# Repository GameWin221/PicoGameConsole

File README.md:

# Shamino Console
My own game console powered by Raspberry Pi Pico and ST7735 LCD display.

### Software Design
The console framework is made to be **elegant**, **readable** and as **performant** as possible. It is written in C++ only for some convenience features and most of it is almost pure embedded-style C. Thanks to the functional and modular code structure it is easy to port it for other platforms.

You can make your own game just by declaring a new `GameInfo` inside `games_list.hpp` file and defining its functions inside other `.cpp` file. (Look at other example games provided in the repository)

### Hardware Design
The new improved version of the "Shamino Console" now features a custom PCB. This greatly improves the general quality of the console. It just looks and feels better now :)

There will be a 3D printed casing for it soon.

To see the old version, look inside the `/old_design` directory.

### Required componnts:
- [Raspberry Pi Pico (W)](https://www.raspberrypi.com/products/raspberry-pi-pico/)

- [Waveshare ST7735 1.8" LCD](https://www.waveshare.com/wiki/1.8inch_LCD_Module)

- [Generic Thumb Joystick](https://botland.store/joystick/1942-thumb-joystick-5904422356231.html)

- 2x [12mm x 12mm Tact Switches](https://botland.store/tact-switch/3663-tact-switch-12x12mm-with-cap-red-mushroom-5pcs-5904422307486.html)

- [Female Connectors for Raspberry Pi Pico](https://botland.store/raspberry-pi-pico-accessories/18863-set-of-female-connectors-for-raspberry-pi-pico-5904422328528.html)

- [5V 12mm Passive Buzzer](https://botland.store/buzzers-sound-generators/18290-buzzer-without-generator-5v-1mm-tht-5904422366025.html)

- ~47Ω Resistor

- ~4,7kΩ Resistor

- [1x8 Goldpin connector](https://botland.store/connectors-goldpin/20031-straight-goldpin-1x40-connector-with-254mm-pitch-black-10pcs-justpi-5904422329198.html)

- (Optional) 2x 5mm M3 Screw to mount the LCD

- 4x 10mm M3 Screws to mount the PCB to the 3D printed casing.

- [Battery Holder for 2x AA batteries **with a power switch** (3x AA batteries will work fine too)](https://botland.store/battery-holders/738-battery-holder-for-2-aa-r6-batteries-with-cover-and-switch-5904422329617.html)

# How to compile? 
### Prerequisites
- [Pico SDK](https://github.com/raspberrypi/pico-sdk) (St the `PICO_SDK_PATH` enviromental variable)
- [ARM Toolchain](https://developer.arm.com/downloads/-/arm-gnu-toolchain-downloads) (Set the `PICO_TOOLCHAIN_PATH` enviromental variable)
- [CMake](https://cmake.org/) (Add to path)
- [MinGW](https://winlibs.com/) or other C++ compiler (Add to path)

### Commands (Using MinGW):
1. `mkdir build && cd build`
2. `cmake -G "MinGW Makefiles" ..`
3. `make` or `mingw32-make`
4. If everything compiled successfully - copy the `GameOnConsole.uf2` file to your Pico

On Windows you can use the `run.bat` script (You will most likely need to specify the target drive which is your Pico)

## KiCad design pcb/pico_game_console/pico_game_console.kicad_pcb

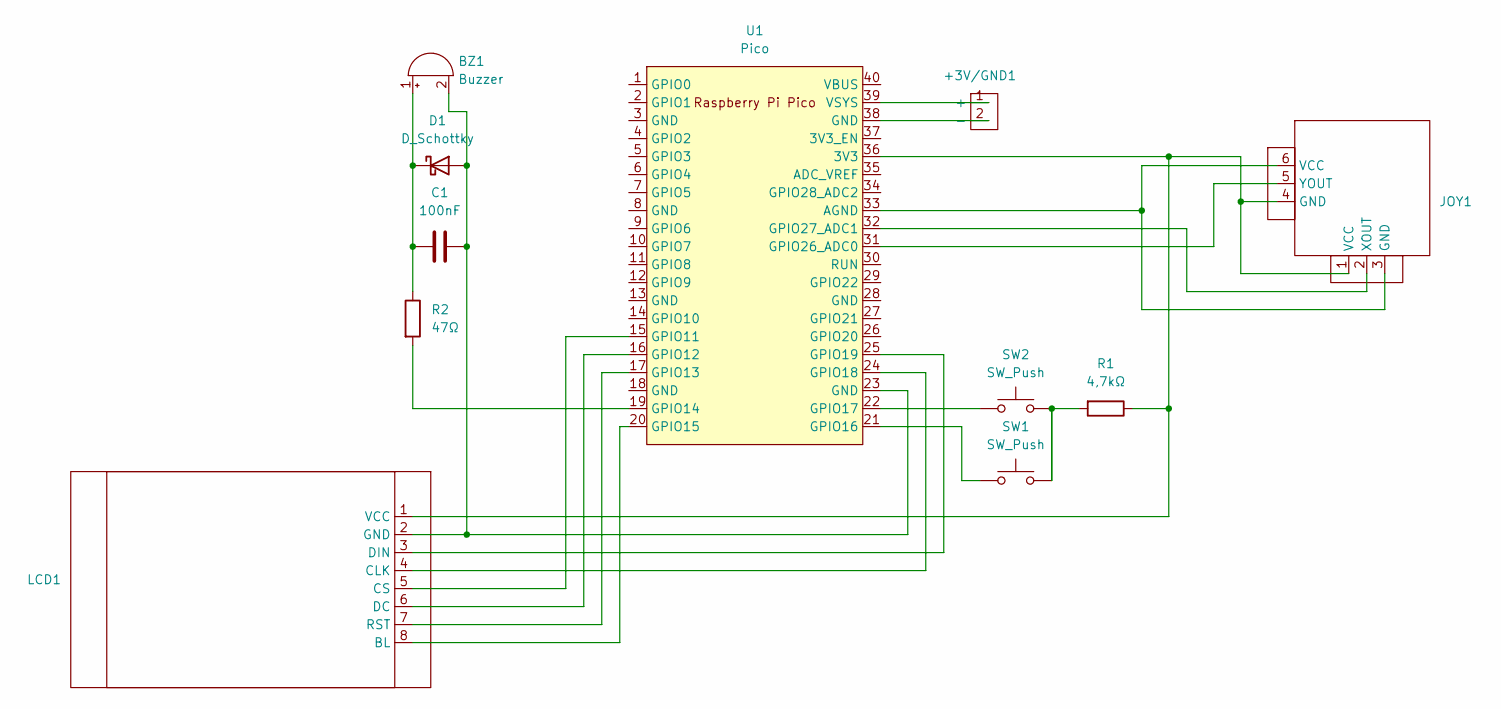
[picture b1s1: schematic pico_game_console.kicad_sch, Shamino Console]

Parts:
+3V/GND1: PowerPins
BZ1: Buzzer; Buzzer_12x9.5RM7.6
C1: 100nF; C_Disc_D5.0mm_W2.5mm_P5.00mm
D1: D_Schottky; D_DO-41_SOD81_P7.62mm_Horizontal
JOY1: Thumb Joystick
LCD1: 1.8Inch_ST7735
R1: 4,7kΩ; R_Axial_DIN0411_L9.9mm_D3.6mm_P12.70mm_Horizontal
R2: 47Ω; R_Axial_DIN0411_L9.9mm_D3.6mm_P12.70mm_Horizontal
SW1, SW2: SW_Push; SW_PUSH-12mm
U1: Pico; RPi_Pico_SMD_TH

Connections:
unnamed: +3V/GND1.1 (+), U1.39 (VSYS)
unnamed: +3V/GND1.2 (-), U1.38 (GND)
unnamed: BZ1.1 (+), C1.1, D1.1 (K), R2.1
unnamed: BZ1.2 (-), C1.2, D1.2 (A), LCD1.2 (GND), U1.23 (GND)
unnamed: JOY1.2 (XOUT), U1.32 (GPIO27_ADC1)
unnamed: JOY1.5 (YOUT), U1.31 (GPIO26_ADC0)
unnamed: LCD1.8 (BL), U1.20 (GPIO15)
unnamed: LCD1.4 (CLK), U1.24 (GPIO18)
unnamed: LCD1.5 (CS), U1.15 (GPIO11)
unnamed: LCD1.6 (DC), U1.16 (GPIO12)
unnamed: LCD1.3 (DIN), U1.25 (GPIO19)
unnamed: LCD1.7 (RST), U1.17 (GPIO13)
unnamed: JOY1.1 (VCC), JOY1.4 (GND), LCD1.1 (VCC), R1.1, U1.36 (3V3)
unnamed: R1.2, SW1.1, SW2.1
unnamed: JOY1.3 (GND), JOY1.6 (VCC), U1.33 (AGND)
unnamed: R2.2, U1.19 (GPIO14)
unnamed: SW1.2, U1.21 (GPIO16)
unnamed: SW2.2, U1.22 (GPIO17)

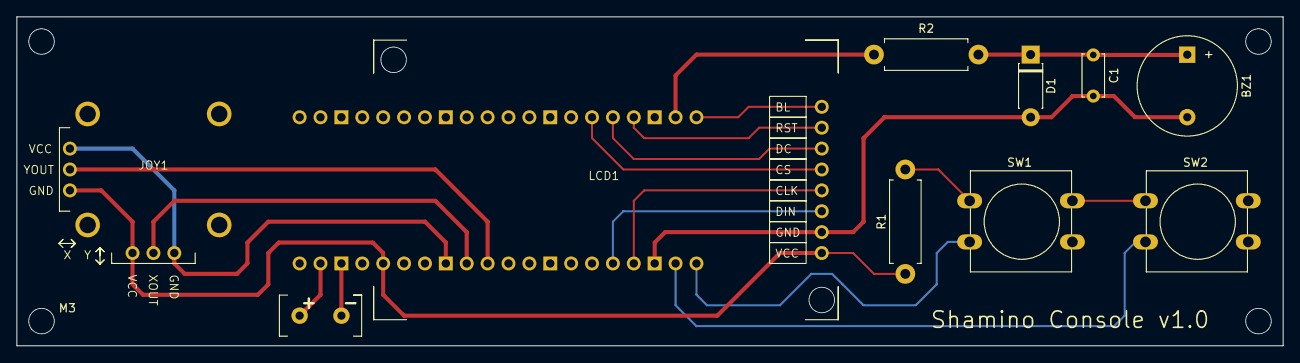
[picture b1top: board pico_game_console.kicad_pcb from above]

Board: 2 copper layers, 154.0 x 40.0 mm, 11 parts (1 on the bottom side), 18 nets.

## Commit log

2023-11-30 Project structure and base framework.
2023-12-02 Final code architecture
2023-12-03 Initial 3D prints and wiring diagram.
2023-12-16 Correct frequency based audio
2023-12-22 Audio Tracks, 3D Game, Center Joystick
2024-04-20 New PCB
2024-04-20 Update to the new version
2024-04-21 Global Config
    Will be gitignored
2024-04-21 Gitignore
2025-07-26 Update LICENSE
